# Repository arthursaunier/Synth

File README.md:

---
permalink: /index.html
layout: home
---

# This repo is being moved to an organization, there will be no new updates on this repo. For more informations, and with designs up to date, go to [BleepSound](https://github.com/orgs/BleepSound/repositories)

# Use all the designs here at your own risk, they have issues.

# Synth

## Not all projects are finished or even perfect, use at your own risks.

### VCOs:

- :exclamation: [CD40106-VCO](vco/cd40106)
    - CD40106 saw core oscillator based on Moritz Klein version (https://www.ericasynths.lv/shop/diy-kits-1/edu-diy-vco/)
        - 4 waveforms
            - Saw
            - Square with PWM control
            - Triangle
            - Sine
        - 5 octave switch
        - 1v/oct CV, FM CV and PWM CV.

### Effects:

- :warning: [StupidBox](stupidbox)
    - (messy directory but everything is there)
    - Size of panels and position is all wrong
    - Distortion module based on StupidBox stompbox design.
    - Vactrol CV to control distortion

### Filters:

- MS20-VCF
    - MS-20 clones built around the LM13700 chip
    - :warning: [Simple MS20 VCF](ms20_vcf/simple):
        - 1 LM13700 filter with a Low pass or High pass switch with CV for cutoff
        - Based on barton's version (https://www.bartonmusicalcircuits.com/synthstuff.html#analog))
    - :heavy_check_mark: [Double MS20-VCF](ms20_vcf/double)
        - 2 filters in one, each with Low pass or High pass with a possibility to bridge them and get a band pass filter with CV for cutoff
        - Based on barton's version (https://www.bartonmusicalcircuits.com/synthstuff.html#analog))

### Drums:

- :heavy_check_mark: [HiHat+Snare](hihat_snare/v1.1)
    - 2 white noise generators with VCAs to create Hihat or Snare sound.
    - Built on the same module, with 2 separate voices (completly independent)
    - No CV
- Drumbox
    - A 4 sounds drumbox built around the CD4011 chip. Bass kick, High and low bonga and claves sound.
    - :heavy_check_mark: V1.0:
        - Each voice has a seperate output.
    - :warning: [V1.2](drumbox):
        - Single main output for the module
        - Push buttons to trigger the voices. The buttons are from THONK (https://www.thonk.co.uk/shop/low-profile-led-buttons/)

### Mixers:

- :heavy_check_mark: [Basic AC mixer](mixers/basic-ac-mixer)
    - 4 channel active mixer with mute option with AC coupling (Audio only)
- :heavy_check_mark: [Basic DC mixer](mixers/basic-dc-mixer)
    - 4 channel active mixer with mute option with DC coupling (Audio+CV)
- Output mixer
    - :warning: [Mono input](mixers/output-mixer/mono_input):
        - 6 channels with 2 mono inputs each, gain and pan on each channel
        - stereo output in jack 3.5mm and jack 6.35mm
        - Headphone output with amp
    - :warning: [Stereo input](mixers/output-mixer/stereo_input):
        - 6 channels with stereo inputs, gain and pan on each channel
        - If only L or R plugged, act as a mono channel
        - stereo output in jack 3.5mm and jack 6.35mm
        - Headphone output with amp

### Multiple:

- :heavy_check_mark: [3x2 multiplexer](multiplexer/3x2)
    - 3x2 multiplexer (3 inputs to 2 output each)
    - cascade the first input to all outputs if no other input is plugged in

### Power delivery:

- :heavy_check_mark:  [PSU](power_supply/psu)
    - Basic +/- 12V power supply built around the L7812/7912 regulators.
-  :heavy_check_mark:  [Distribution board](power_supply/distributionboard)
    - Basic PSU distribution board, with 10 IDC headers.

### Sequencers:

- :exclamation: [Drum trigger sequencer](trigger_sequencer)
    - Based off the Big Button from LMNC, with an arduino Nano.
    - No code developped yet
    - Not finished and probably never will :)

| Symbol | Description |
| ----------- | ----------- |
| :heavy_check_mark: | Fully designed, debugged, tested, and verified. |
| :warning: | Fully designed but not tested. There is a high chance this won't work first try. |
| :exclamation: | Unfinished, messy design. Do not use, for reference or otherwise. |

*Cheers to @Sonosus for the labeling idea*

This work is licensed under a [Creative Commons Attribution-ShareAlike 4.0 International License.](http://creativecommons.org/licenses/by-sa/4.0/)

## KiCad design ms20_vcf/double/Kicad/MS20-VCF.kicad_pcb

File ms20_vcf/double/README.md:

---
permalink: /ms20_vcf/double/index.html
layout: single
---

# Double MS20 VCF

2 filters in one with a possibility to bridge them and get a band pass filter.

When using the band pass mode, signal IN on filter 1 and out on filter 2.

For each filter :

- Ms20-VCF clone based on BartonSynth version.

- cutoff + resonance, with a switch to chose low pass or high pass mode.

- CV control on the filter cutoff.

- Self oscilation if resonance pushed to maximum, can be adjusted with 2 trimmers  on each filter.

    - 1 trimmer for the sine wave amplitude (resVol)
    - 1 trimmer for the level at which the knob for resonance starts the self oscillation (resLvl)

Uses an DIP LM13700 not produced anymore, Will do an SMD version soon.

Regular build, I use ceramic capacitors but you can use film/polyester.

[See bom](bom/ibom.html)

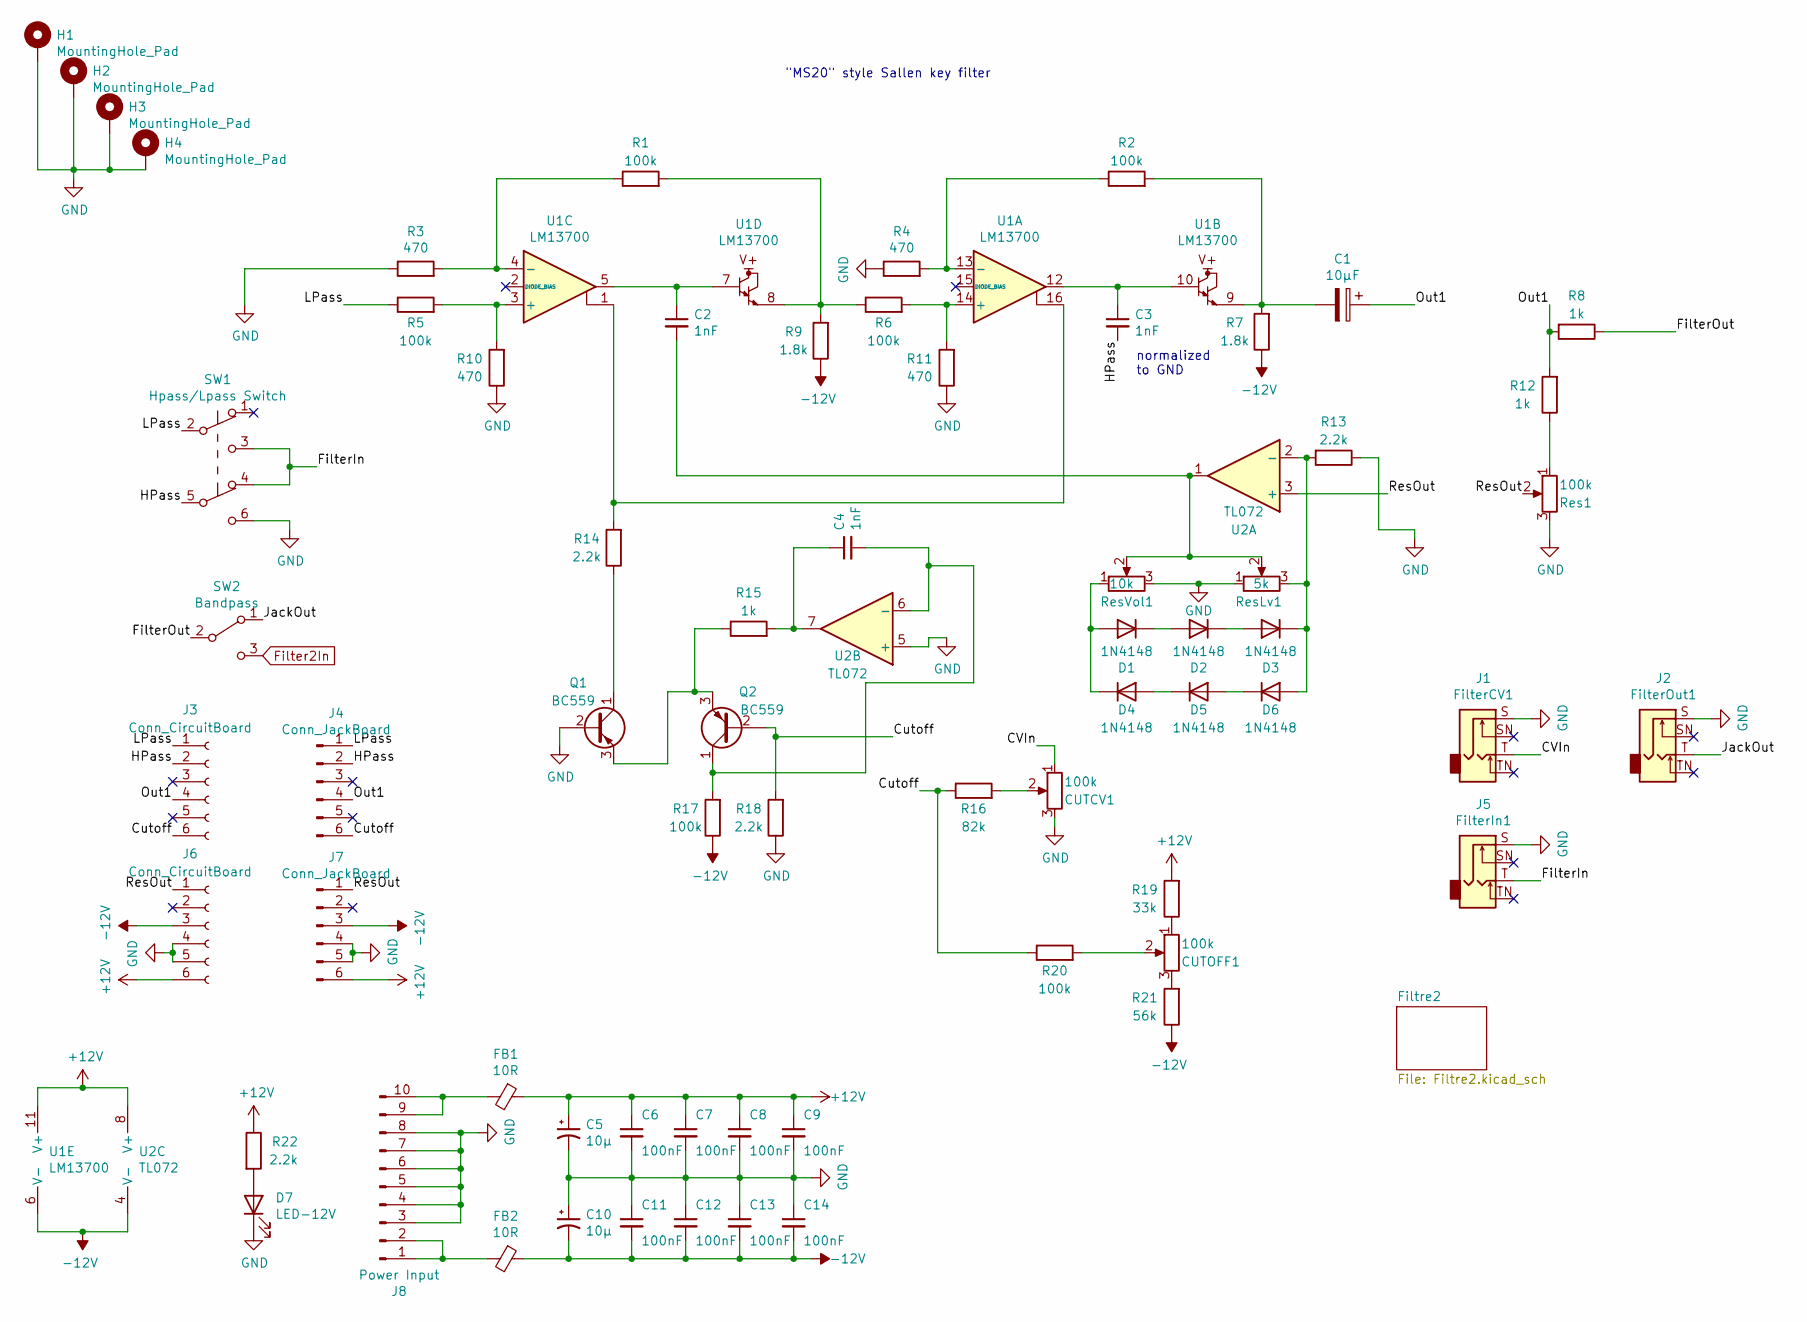
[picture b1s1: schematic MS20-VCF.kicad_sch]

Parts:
C1: 10µF; CP_Radial_D5.0mm_P2.00mm
C2, C3, C4: 1nF; C_Disc_D7.0mm_W2.5mm_P5.00mm
C5, C10: 10µ; CP_Radial_D5.0mm_P2.00mm
C6, C7, C8, C9, C11, C12, C13, C14: 100nF; C_Disc_D7.0mm_W2.5mm_P5.00mm
CUTCV1: 100k; Pot-bourns-alpha
CUTOFF1: 100k; Pot-bourns-alpha
D1, D2, D3, D4, D5, D6: 1N4148; D_DO-35_SOD27_P7.62mm_Horizontal
D7: LED-12V; LED_D4.0mm
FB1, FB2: 10R; L_Axial_L7.0mm_D3.3mm_P10.16mm_Horizontal_Fastron_MICC
H1, H2, H3, H4: MountingHole_Pad; Doepfer Mounting hole
J1: FilterCV1; Thonkiconn
J2: FilterOut1; Thonkiconn
J3, J6: Conn_CircuitBoard; PinSocket_1x06_P2.54mm_Vertical
J4, J7: Conn_JackBoard; PinHeader_1x06_P2.54mm_Vertical
J5: FilterIn1; Thonkiconn
J8: Power Input; IDC-Header_2x05_P2.54mm_Vertical
Q1, Q2: BC559; TO-92_Inline_Wide
R1, R2, R5, R6, R17, R20: 100k; R_Axial_DIN0207_L6.3mm_D2.5mm_P10.16mm_Horizontal
R3, R4, R10, R11: 470; R_Axial_DIN0207_L6.3mm_D2.5mm_P10.16mm_Horizontal
R7, R9: 1.8k; R_Axial_DIN0207_L6.3mm_D2.5mm_P10.16mm_Horizontal
R8, R12, R15: 1k; R_Axial_DIN0207_L6.3mm_D2.5mm_P10.16mm_Horizontal
R13, R14, R18, R22: 2.2k; R_Axial_DIN0207_L6.3mm_D2.5mm_P10.16mm_Horizontal
R16: 82k; R_Axial_DIN0207_L6.3mm_D2.5mm_P10.16mm_Horizontal
R19: 33k; R_Axial_DIN0207_L6.3mm_D2.5mm_P10.16mm_Horizontal
R21: 56k; R_Axial_DIN0207_L6.3mm_D2.5mm_P10.16mm_Horizontal
Res1: 100k; Pot-bourns-alpha
ResLv1: 5k; Potentiometer_Bourns_3386X_Horizontal
ResVol1: 10k; Potentiometer_Bourns_3386X_Horizontal
SW1: Hpass/Lpass Switch; SW_DPDT_Toggle
SW2: Bandpass; SW_Toggle_Blue_wSlots
U1: LM13700; SOIC-16_3.9x9.9mm_P1.27mm
U2: TL072; DIP-8_W7.62mm_Socket

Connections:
+12V: C5.1, C6.1, C7.1, C8.1, C9.1, FB1.1, J6.6, J7.6, R19.2, R22.1, U1.11 (V+), U2.8 (V+); also elsewhere on the board
-12V: C10.2, C11.2, C12.2, C13.2, C14.2, FB2.1, J6.3, J7.3, R7.1, R9.1, R17.1, R21.1, U1.6 (V-), U2.4 (V-); also elsewhere on the board
/CVIn: CUTCV1.1, J1.T
/Cutoff: J3.6, J4.6, Q2.2 (B), R16.1, R18.2, R20.1
/FilterIn: J5.T, SW1.3 (C), SW1.4 (A)
/FilterOut: R8.1, SW2.2 (B)
/HPass: C3.2, J3.2, J4.2, SW1.5 (B)
/JackOut: J2.T, SW2.1 (A)
/LPass: J3.1, J4.1, R5.1, SW1.2 (B)
/Out1: C1.1, J3.4, J4.4, R8.2, R12.2
/ResOut: J6.1, J7.1, Res1.2, U2.3 (+)
Filter2In: SW2.3 (C); also elsewhere on the board
GND: C5.2, C6.2, C7.2, C8.2, C9.2, C10.1, C11.1, C12.1, C13.1, C14.1, CUTCV1.3, D7.1 (K), H1.1, H2.1, H3.1, H4.1, J1.S, J2.S, J5.S, J6.4, J6.5, J7.4, J7.5, J8.3, J8.4, J8.5, J8.6, J8.7, J8.8, Q1.2 (B), R3.1, R4.1, R10.1, R11.1, R13.1, R18.1, Res1.3, ResLv1.1, ResVol1.3, SW1.6 (C), U2.5 (+); also elsewhere on the board
unnamed: C1.2, R2.2, R7.2, U1.9
unnamed: C2.1, U1.5, U1.7
unnamed: C2.2, ResLv1.2, ResVol1.2, U2.1
unnamed: C3.1, U1.10, U1.12
unnamed: C4.1, R15.2, U2.7
unnamed: C4.2, Q2.1 (C), R17.2, U2.6 (-)
unnamed: CUTCV1.2, R16.2
unnamed: CUTOFF1.1, R19.1
unnamed: D1.1 (K), D2.2 (A)
unnamed: D1.2 (A), D4.1 (K), ResVol1.1
unnamed: D2.1 (K), D3.2 (A)
unnamed: D3.1 (K), D6.2 (A), R13.2, ResLv1.3, U2.2 (-)
unnamed: D4.2 (A), D5.1 (K)
unnamed: D5.2 (A), D6.1 (K)
unnamed: D7.2 (A), R22.2
unnamed: FB1.2, J8.9, J8.10
unnamed: FB2.2, J8.1, J8.2
unnamed: Q1.1 (C), R14.1
unnamed: Q1.3 (E), Q2.3 (E), R15.1
unnamed: R1.1, R3.2, U1.4 (-)
unnamed: R1.2, R6.1, R9.2, U1.8
unnamed: R2.1, R4.2, U1.13 (-)
unnamed: R5.2, R10.2, U1.3 (+)
unnamed: R6.2, R11.2, U1.14 (+)
unnamed: R12.1, Res1.1
unnamed: R14.2, U1.1, U1.16
unnamed: CUTOFF1.2, R20.2
unnamed: CUTOFF1.3, R21.2

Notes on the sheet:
normalized to GND
"MS20" style Sallen key filter

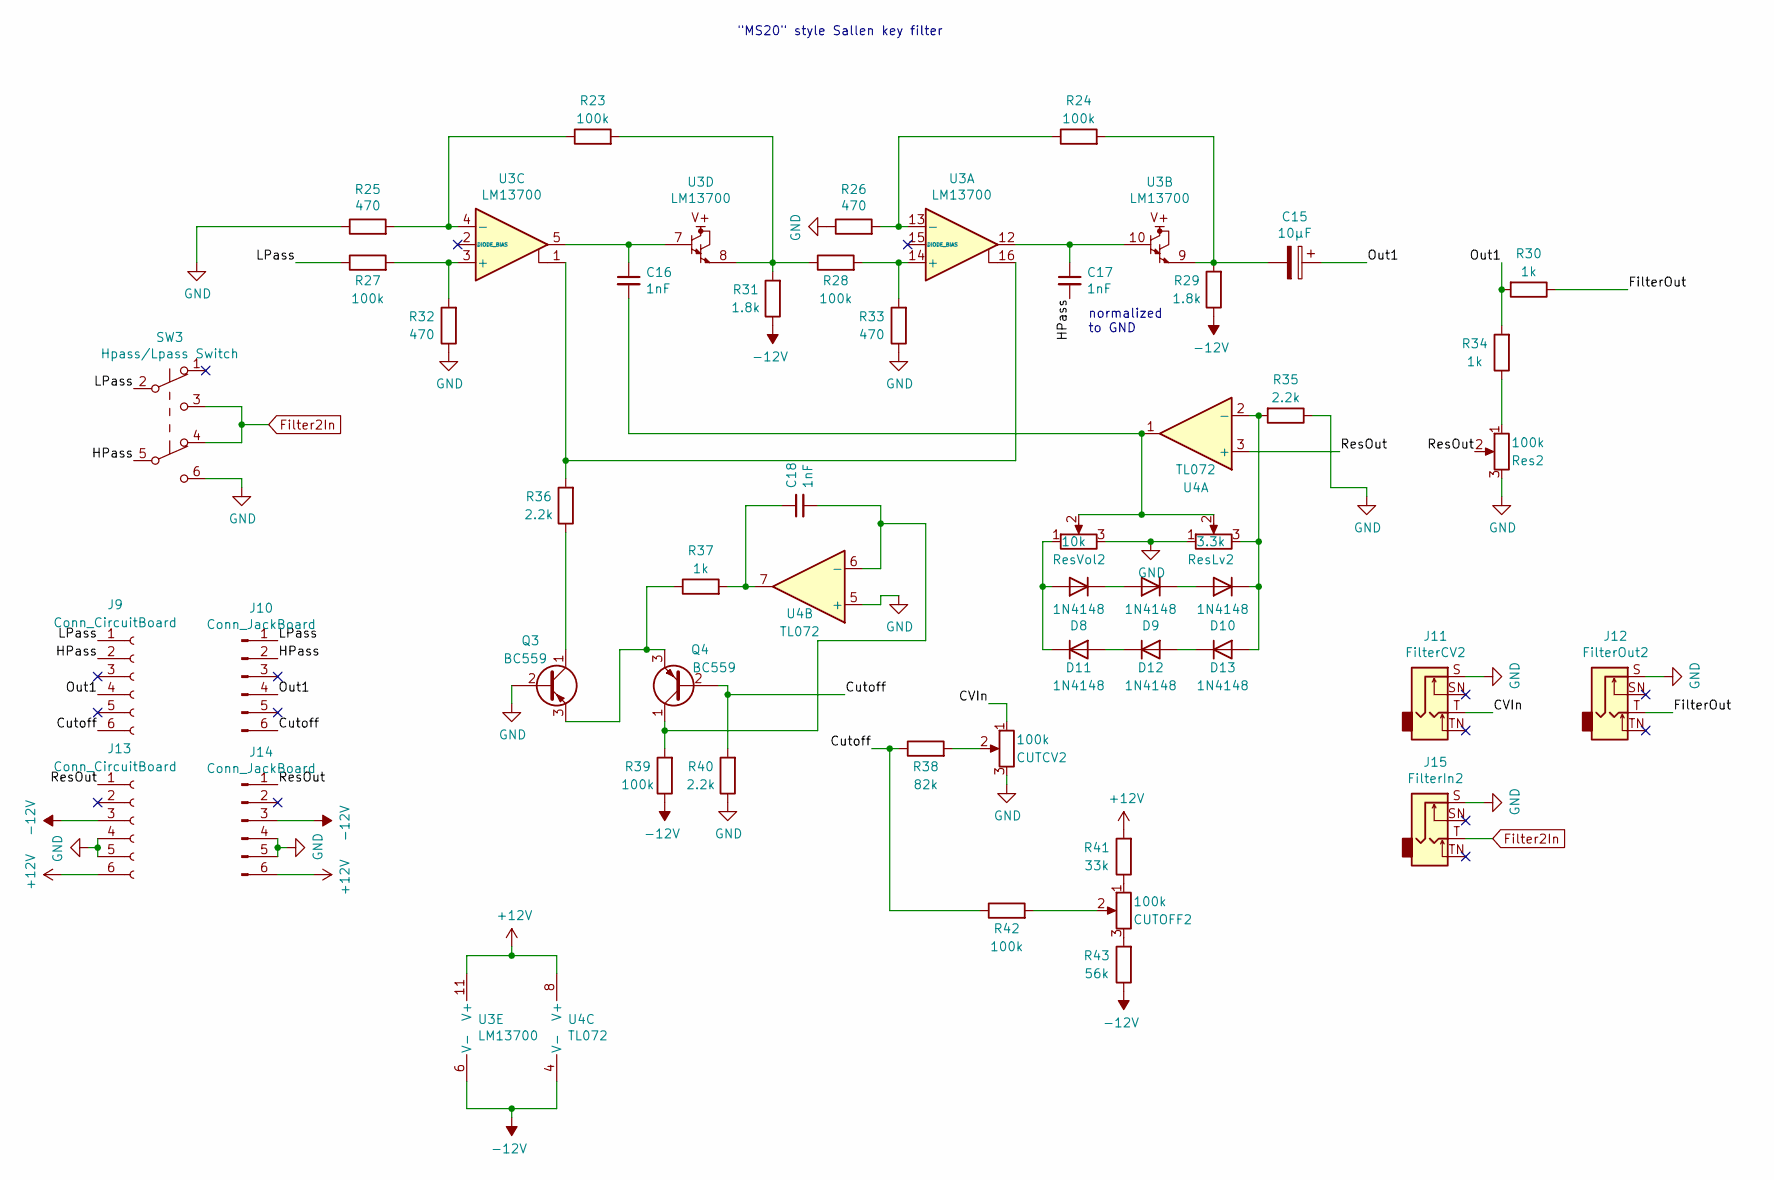
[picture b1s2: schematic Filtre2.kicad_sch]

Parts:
C15: 10µF; CP_Radial_D5.0mm_P2.00mm
C16, C17, C18: 1nF; C_Disc_D7.0mm_W2.5mm_P5.00mm
CUTCV2: 100k; Pot-bourns-alpha
CUTOFF2: 100k; Pot-bourns-alpha
D8, D9, D10, D11, D12, D13: 1N4148; D_DO-35_SOD27_P7.62mm_Horizontal
J9, J13: Conn_CircuitBoard; PinSocket_1x06_P2.54mm_Vertical
J10, J14: Conn_JackBoard; PinHeader_1x06_P2.54mm_Vertical
J11: FilterCV2; Thonkiconn
J12: FilterOut2; Thonkiconn
J15: FilterIn2; Thonkiconn
Q3, Q4: BC559; TO-92_Inline_Wide
R23, R24, R27, R28, R39, R42: 100k; R_Axial_DIN0207_L6.3mm_D2.5mm_P10.16mm_Horizontal
R25, R26, R32, R33: 470; R_Axial_DIN0207_L6.3mm_D2.5mm_P10.16mm_Horizontal
R29, R31: 1.8k; R_Axial_DIN0207_L6.3mm_D2.5mm_P10.16mm_Horizontal
R30, R34, R37: 1k; R_Axial_DIN0207_L6.3mm_D2.5mm_P10.16mm_Horizontal
R35, R36, R40: 2.2k; R_Axial_DIN0207_L6.3mm_D2.5mm_P10.16mm_Horizontal
R38: 82k; R_Axial_DIN0207_L6.3mm_D2.5mm_P10.16mm_Horizontal
R41: 33k; R_Axial_DIN0207_L6.3mm_D2.5mm_P10.16mm_Horizontal
R43: 56k; R_Axial_DIN0207_L6.3mm_D2.5mm_P10.16mm_Horizontal
Res2: 100k; Pot-bourns-alpha
ResLv2: 3.3k; Potentiometer_Bourns_3386X_Horizontal
ResVol2: 10k; Potentiometer_Bourns_3386X_Horizontal
SW3: Hpass/Lpass Switch; SW_DPDT_Toggle
U3: LM13700; SOIC-16_3.9x9.9mm_P1.27mm
U4: TL072; DIP-8_W7.62mm_Socket

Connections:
+12V: J13.6, J14.6, R41.2, U3.11 (V+), U4.8 (V+); also elsewhere on the board
-12V: J13.3, J14.3, R29.1, R31.1, R39.1, R43.1, U3.6 (V-), U4.4 (V-); also elsewhere on the board
/Filtre2/CVIn: CUTCV2.1, J11.T
/Filtre2/Cutoff: J9.6, J10.6, Q4.2 (B), R38.1, R40.2, R42.1
/Filtre2/FilterOut: J12.T, R30.1
/Filtre2/HPass: C17.2, J9.2, J10.2, SW3.5 (B)
/Filtre2/LPass: J9.1, J10.1, R27.1, SW3.2 (B)
/Filtre2/Out1: C15.1, J9.4, J10.4, R30.2, R34.2
/Filtre2/ResOut: J13.1, J14.1, Res2.2, U4.3 (+)
Filter2In: J15.T, SW3.3 (C), SW3.4 (A); also elsewhere on the board
GND: CUTCV2.3, J11.S, J12.S, J13.4, J13.5, J14.4, J14.5, J15.S, Q3.2 (B), R25.1, R26.1, R32.1, R33.1, R35.1, R40.1, Res2.3, ResLv2.1, ResVol2.3, SW3.6 (C), U4.5 (+); also elsewhere on the board
unnamed: C15.2, R24.2, R29.2, U3.9
unnamed: C16.1, U3.5, U3.7
unnamed: C16.2, ResLv2.2, ResVol2.2, U4.1
unnamed: C17.1, U3.10, U3.12
unnamed: C18.1, R37.2, U4.7
unnamed: C18.2, Q4.1 (C), R39.2, U4.6 (-)
unnamed: CUTCV2.2, R38.2
unnamed: CUTOFF2.1, R41.1
unnamed: CUTOFF2.2, R42.2
unnamed: CUTOFF2.3, R43.2
unnamed: D8.1 (K), D9.2 (A)
unnamed: D10.1 (K), D13.2 (A), R35.2, ResLv2.3, U4.2 (-)
unnamed: D9.1 (K), D10.2 (A)
unnamed: D8.2 (A), D11.1 (K), ResVol2.1
unnamed: D11.2 (A), D12.1 (K)
unnamed: D12.2 (A), D13.1 (K)
unnamed: Q3.1 (C), R36.1
unnamed: Q3.3 (E), Q4.3 (E), R37.1
unnamed: R23.1, R25.2, U3.4 (-)
unnamed: R23.2, R28.1, R31.2, U3.8
unnamed: R24.1, R26.2, U3.13 (-)
unnamed: R27.2, R32.2, U3.3 (+)
unnamed: R28.2, R33.2, U3.14 (+)
unnamed: R34.1, Res2.1
unnamed: R36.2, U3.1, U3.16

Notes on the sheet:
normalized to GND
"MS20" style Sallen key filter

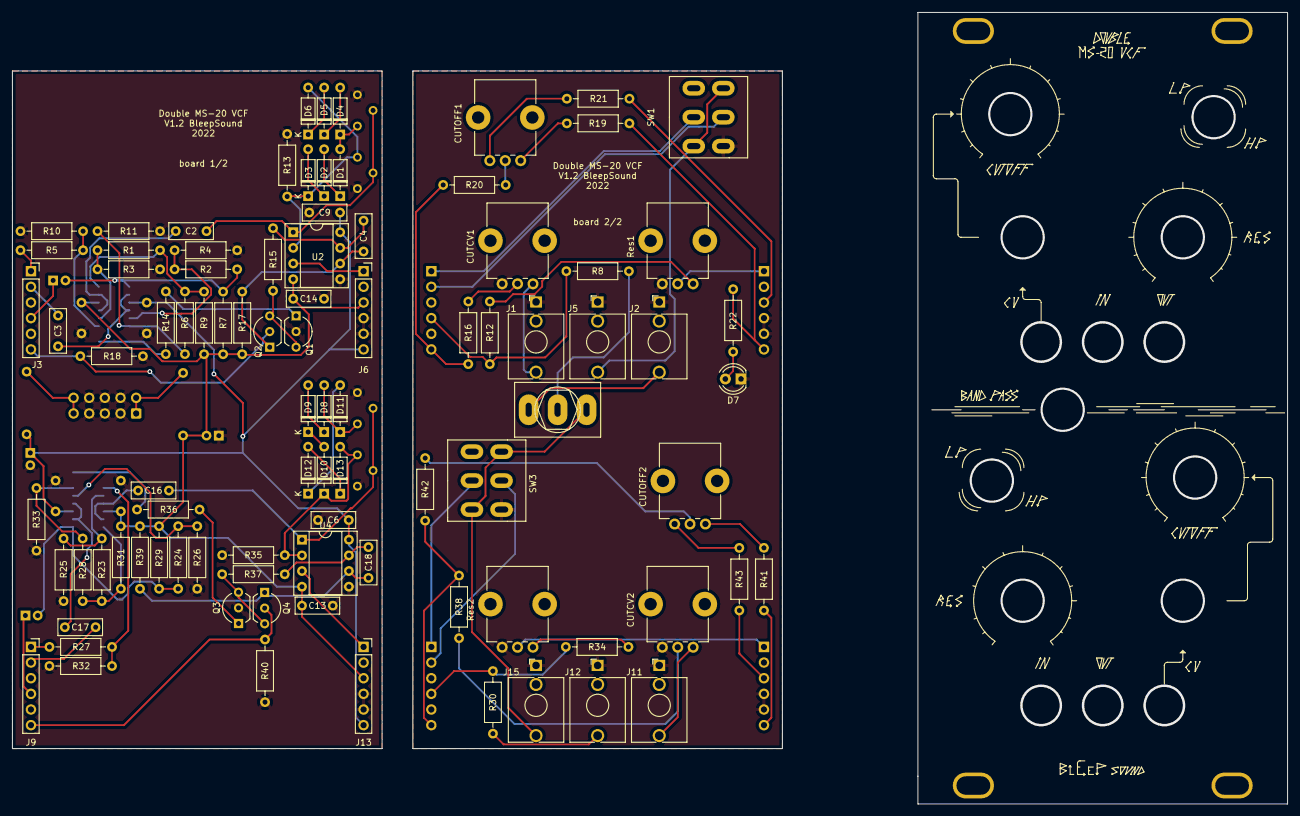
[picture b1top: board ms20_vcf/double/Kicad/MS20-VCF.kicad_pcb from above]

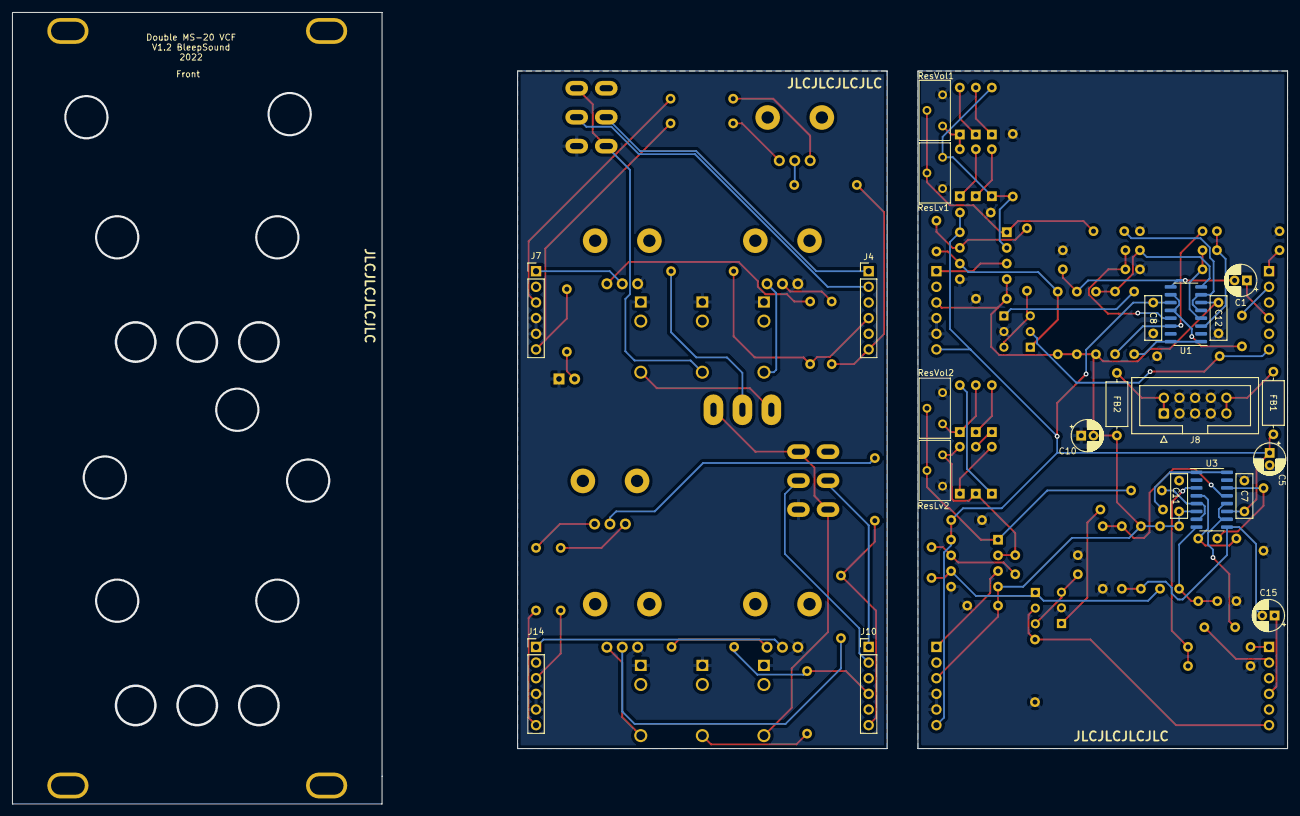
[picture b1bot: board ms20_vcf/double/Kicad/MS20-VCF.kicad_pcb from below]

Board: 2 copper layers, 207.0 x 128.5 mm, 116 parts (21 on the bottom side), 73 nets.

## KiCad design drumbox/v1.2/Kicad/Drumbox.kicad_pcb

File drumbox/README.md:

# Drumbox

## V1.0

A 4 sounds drumbox built around the CD4011 chip. Bass kick, High and low bonga and claves sound.

Each voice has a seperate output.

No CV

## V1.1

Single main output for the module

Push buttons to trigger the voices. The buttons are from THONK (https://www.thonk.co.uk/shop/low-profile-led-buttons/)

## V1.2

This version adds a gain change of the output buffers on each voice.

[See bom](v1.2/bom/ibom.html)

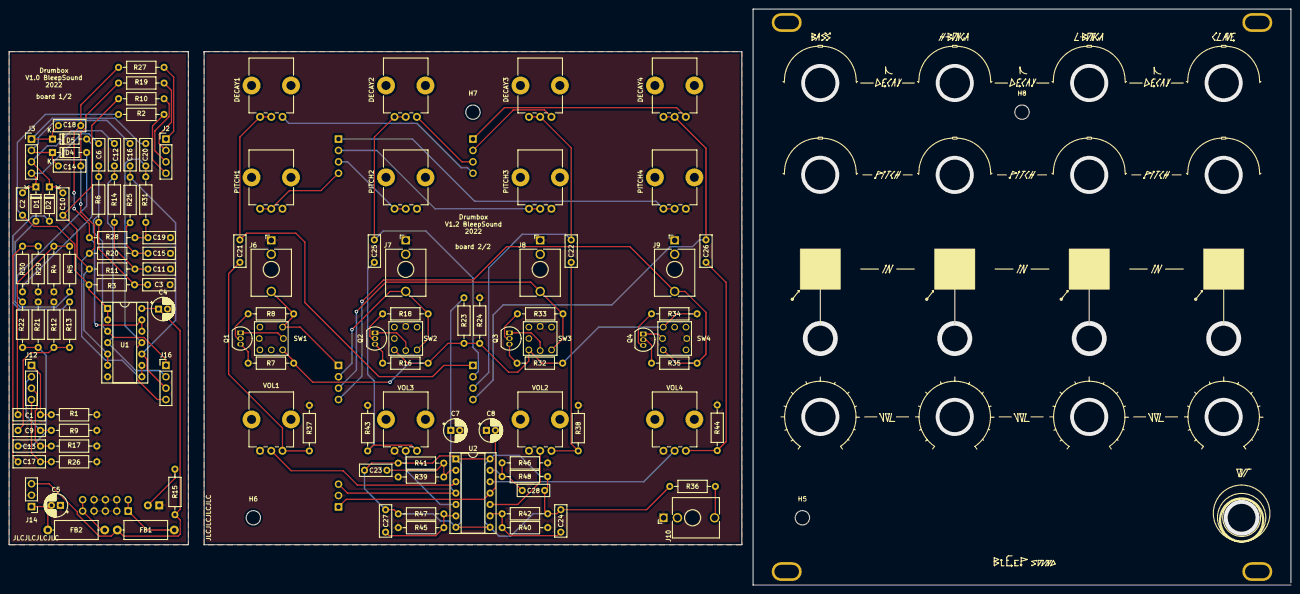
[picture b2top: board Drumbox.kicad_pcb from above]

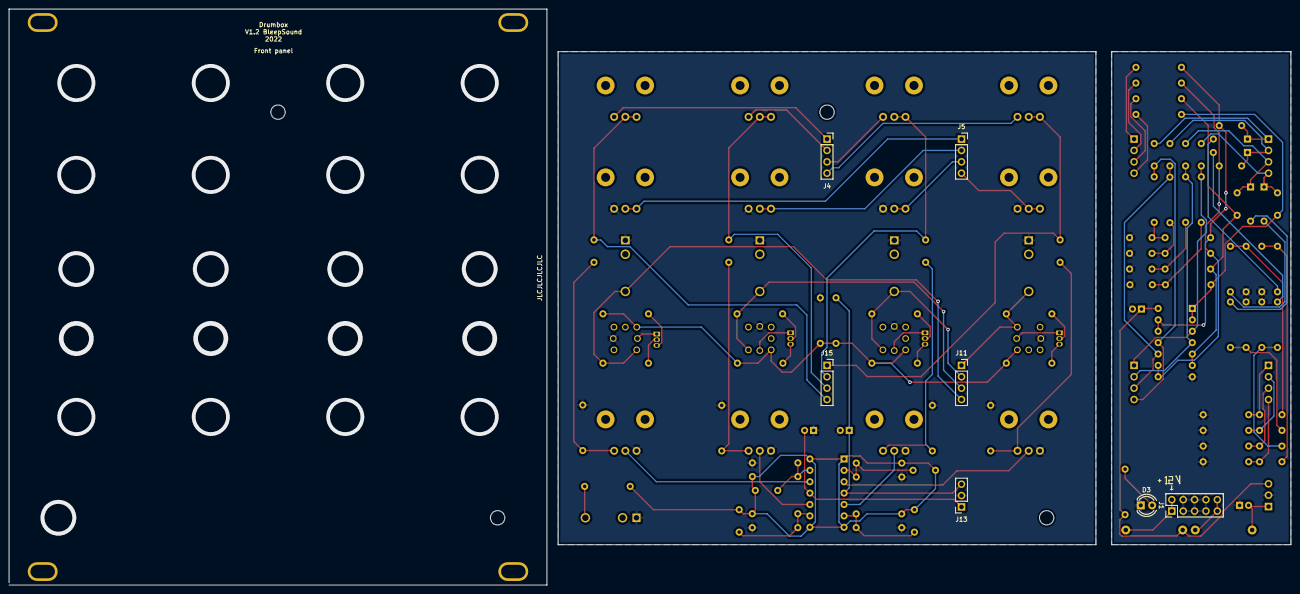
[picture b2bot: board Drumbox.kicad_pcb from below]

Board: 2 copper layers, 286.0 x 128.5 mm, 129 parts (7 on the bottom side), 65 nets.

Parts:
C1, C3: 150nF; C_Disc_D7.0mm_W2.5mm_P5.00mm
C2, C6: 47nF; C_Disc_D7.0mm_W2.5mm_P5.00mm
C4, C5: 10µ; CP_Radial_D5.0mm_P2.00mm
C7, C8: 100n; CP_Radial_D5.0mm_P2.00mm
C9, C11: 33nF; C_Disc_D7.0mm_W2.5mm_P5.00mm
C10, C12: 10nF; C_Disc_D7.0mm_W2.5mm_P5.00mm
C13, C15: 39nF; C_Disc_D7.0mm_W2.5mm_P5.00mm
C14, C16: 12nF; C_Disc_D7.0mm_W2.5mm_P5.00mm
C17: 4.7nF; C_Disc_D7.0mm_W2.5mm_P5.00mm
C18, C20: 1.5nF; C_Disc_D7.0mm_W2.5mm_P5.00mm
C19: 56nF; C_Disc_D7.0mm_W2.5mm_P5.00mm
C21, C22, C25, C26: .1µF; C_Disc_D7.0mm_W2.5mm_P5.00mm
C23, C24, C27, C28: 22pF; C_Disc_D7.0mm_W2.5mm_P5.00mm
D1, D2, D4, D5: 1N4148; D_DO-35_SOD27_P7.62mm_Horizontal
D3: LED-12V; LED_D4.0mm
DECAY1, DECAY2, DECAY3, DECAY4: 470k; Potentiometer_Bourns_PTV09A-1_Single_Vertical
FB1, FB2: 10R; L_Axial_L9.5mm_D4.0mm_P12.70mm_Horizontal_Fastron_SMCC
H1, H2, H3, H4: MountingHole; Doepfer Mounting hole
H5, H6, H7, H8: SpacerHoles; MountingHole_3.2mm_M3
J1: Power Input; PinHeader_2x05_P2.54mm_Vertical
J2, J3, J12, J16: Conn_01x04_Male; PinHeader_1x04_P2.54mm_Vertical
J4, J5, J11, J15: Conn_01x04_Female; PinSocket_1x04_P2.54mm_Vertical
J6: Bass IN; Jack_3.5mm_QingPu_WQP-PJ398SM_Vertical_CircularHoles
J7: HBonga IN; Jack_3.5mm_QingPu_WQP-PJ398SM_Vertical_CircularHoles
J8: LBonga IN; Jack_3.5mm_QingPu_WQP-PJ398SM_Vertical_CircularHoles
J9: Clave IN; Jack_3.5mm_QingPu_WQP-PJ398SM_Vertical_CircularHoles
J10: Main OUT; Jack_3.5mm_QingPu_WQP-PJ398SM_Vertical_CircularHoles
J13: Conn_01x03_Female; PinSocket_1x03_P2.54mm_Vertical
J14: Conn_01x03_Male; PinHeader_1x03_P2.54mm_Vertical
PITCH1, PITCH2, PITCH3, PITCH4: 10k; Potentiometer_Bourns_PTV09A-1_Single_Vertical
Q1, Q2, Q3, Q4: 2N3904; TO-92_Inline
R1, R9, R17, R26: 12k; R_Axial_DIN0207_L6.3mm_D2.5mm_P10.16mm_Horizontal
R2, R10, R19, R27: 150k; R_Axial_DIN0207_L6.3mm_D2.5mm_P10.16mm_Horizontal
R3, R6, R11, R14, R20, R25, R28, R31: 68k; R_Axial_DIN0207_L6.3mm_D2.5mm_P10.16mm_Horizontal
R4, R12, R21, R23, R29: 47k; R_Axial_DIN0207_L6.3mm_D2.5mm_P10.16mm_Horizontal
R5, R13, R22, R30: 27k; R_Axial_DIN0207_L6.3mm_D2.5mm_P10.16mm_Horizontal
R7, R16, R32, R34, R36: 1k; R_Axial_DIN0207_L6.3mm_D2.5mm_P10.16mm_Horizontal
R8, R18, R33, R35, R41, R42, R47, R48: 100k; R_Axial_DIN0207_L6.3mm_D2.5mm_P10.16mm_Horizontal
R15: 2.2k; R_Axial_DIN0207_L6.3mm_D2.5mm_P10.16mm_Horizontal
R24: 33k; R_Axial_DIN0207_L6.3mm_D2.5mm_P10.16mm_Horizontal
R37, R38, R43, R44: 1M; R_Axial_DIN0207_L6.3mm_D2.5mm_P10.16mm_Horizontal
R39: 10k; R_Axial_DIN0207_L6.3mm_D2.5mm_P10.16mm_Horizontal
R40, R45, R46: 20k; R_Axial_DIN0207_L6.3mm_D2.5mm_P10.16mm_Horizontal
SW1, SW2, SW3, SW4: SW_MEC_LOW_PROF_LED; PB01-109TL
U1: 4011; DIP-14_W7.62mm_Socket
U2: TL074; DIP-14_W7.62mm_Socket
VOL1, VOL2, VOL3, VOL4: 10k; Potentiometer_Bourns_PTV09A-1_Single_Vertical

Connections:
+5V: R7.1, R16.1, R23.2, R24.1, R32.1, R34.1, SW1.1, SW2.1, SW3.1, SW4.1
+12V: C4.1, C7.1, FB1.1, J13.3, J14.3, R15.1, R23.1, U1.14 (VDD), U2.4 (V+)
-12V: C5.2, C8.2, FB2.1, J13.1, J14.1, U2.11 (V-)
DEIn1: DECAY1.1, J2.4, J4.4, R2.1
DEIn2: DECAY2.1, J2.3, J4.3, R10.1
DEIn3: DECAY3.1, J2.2, J4.2, R19.1
DEIn4: DECAY4.1, J2.1, J4.1, R27.1
GND: C3.2, C4.2, C5.1, C7.2, C8.1, C11.2, C15.2, C19.2, D3.1 (K), J1.3, J1.4, J1.5, J1.6, J1.7, J1.8, J6.S, J7.S, J8.S, J9.S, J10.S, J13.2, J14.2, PITCH1.1, PITCH2.1, PITCH3.1, PITCH4.1, R1.2, R4.1, R9.2, R12.1, R17.2, R21.1, R24.2, R26.2, R29.1, R37.2, R38.2, R39.2, R40.2, R43.2, R44.2, R45.2, R46.2, SW1.L2, SW2.L2, SW3.L2, SW4.L2, U1.7 (VSS), VOL1.3, VOL2.3, VOL3.3, VOL4.3
In1: C1.1, J6.T, J11.1, J12.1, R1.1, R8.1, SW1.3
In2: C9.1, J7.T, J11.2, J12.2, R9.1, R18.1, SW2.3
In3: C13.1, J8.T, J11.3, J12.3, R17.1, R33.1, SW3.3
In4: C17.1, J9.T, J11.4, J12.4, R26.1, R35.1, SW4.3
unnamed: C1.2, R4.2, R5.1
unnamed: C2.1, R2.2, R3.2, U1.1, U1.2
unnamed: C3.1, R3.1, R6.2
unnamed: C9.2, R12.2, R13.1
unnamed: C10.1, R10.2, R11.2, U1.5, U1.6
unnamed: C11.1, R11.1, R14.2
unnamed: C13.2, R21.2, R22.1
unnamed: C14.1, R19.2, R20.2, U1.8, U1.9
unnamed: C15.1, R20.1, R25.2
unnamed: C17.2, R29.2, R30.1
unnamed: C18.1, R27.2, R28.2, U1.12, U1.13
unnamed: C19.1, R28.1, R31.2
unnamed: C21.2, R37.1, VOL1.1
unnamed: C22.2, R38.1, VOL2.1
unnamed: C23.1, R39.1, R41.2, U2.2 (-)
unnamed: C24.1, R40.1, R42.2, U2.9 (-)
unnamed: C25.2, R43.1, VOL3.1
unnamed: C26.2, R44.1, VOL4.1
unnamed: C27.1, R45.1, R47.2, U2.6 (-)
unnamed: C28.1, R46.1, R48.2, U2.13 (-)
unnamed: D1.2 (A), R5.2
unnamed: D2.2 (A), R13.2
unnamed: D3.2 (A), R15.2
unnamed: D4.2 (A), R22.2
unnamed: D5.2 (A), R30.2
unnamed: FB1.2, J1.1, J1.2
unnamed: FB2.2, J1.9, J1.10
unnamed: J10.T, R36.1
unnamed: Q1.1 (E), SW1.L1
unnamed: Q1.2 (B), R8.2
unnamed: Q1.3 (C), R7.2
unnamed: Q2.1 (E), SW2.L1
unnamed: Q2.2 (B), R18.2
unnamed: Q2.3 (C), R16.2
unnamed: Q3.1 (E), SW3.L1
unnamed: Q3.2 (B), R33.2
unnamed: Q3.3 (C), R32.2
unnamed: Q4.1 (E), SW4.L1
unnamed: Q4.2 (B), R35.2
unnamed: Q4.3 (C), R34.2
unnamed: U2.3 (+), VOL1.2
unnamed: U2.5 (+), VOL3.2
unnamed: U2.10 (+), VOL2.2
unnamed: U2.12 (+), VOL4.2
O1: C6.2, C21.1, DECAY1.2, DECAY1.3, J15.1, J16.1, R6.1, U1.3
O2: C12.2, C25.1, DECAY2.2, DECAY2.3, J15.2, J16.2, R14.1, U1.4
O3: C16.2, C22.1, DECAY3.2, DECAY3.3, J15.3, J16.3, R25.1, U1.10
O4: C20.2, C26.1, DECAY4.2, DECAY4.3, J15.4, J16.4, R31.1, U1.11
Out1: C23.2, C24.2, C27.2, C28.2, R36.2, R41.1, R42.1, R47.1, R48.1, U2.1, U2.7, U2.8, U2.14
PIOut1: C2.2, C6.1, D1.1 (K), J3.4, J5.4, PITCH1.2, PITCH1.3
PIOut2: C10.2, C12.1, D2.1 (K), J3.3, J5.3, PITCH2.2, PITCH2.3
PIOut3: C14.2, C16.1, D4.1 (K), J3.2, J5.2, PITCH3.2, PITCH3.3
PIOut4: C18.2, C20.1, D5.1 (K), J3.1, J5.1, PITCH4.2, PITCH4.3

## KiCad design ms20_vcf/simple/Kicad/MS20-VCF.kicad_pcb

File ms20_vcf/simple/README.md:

---
permalink: /ms20_vcf/simple/index.html
layout: single
---

# MS20 VCF

Ms20-VCF clone based on BartonSynth version.

cutoff + resonance, with a switch to chose low pass or high pass mode.

CV control on the filter cutoff.

Self oscilation if resonance pushed to maximum, can be adjusted with 2 trimmers :

- 1 trimmer for the sine wave amplitude (resVol)
- 1 trimmer for the level at which the knob for resonance starts the self oscillation (resLvl)

Uses an SMD LM13700 because the DIP ones are not produced anymore.

Regular build, I use ceramic capacitors but you can use film/polyester.

[See bom](bom/ibom.html)

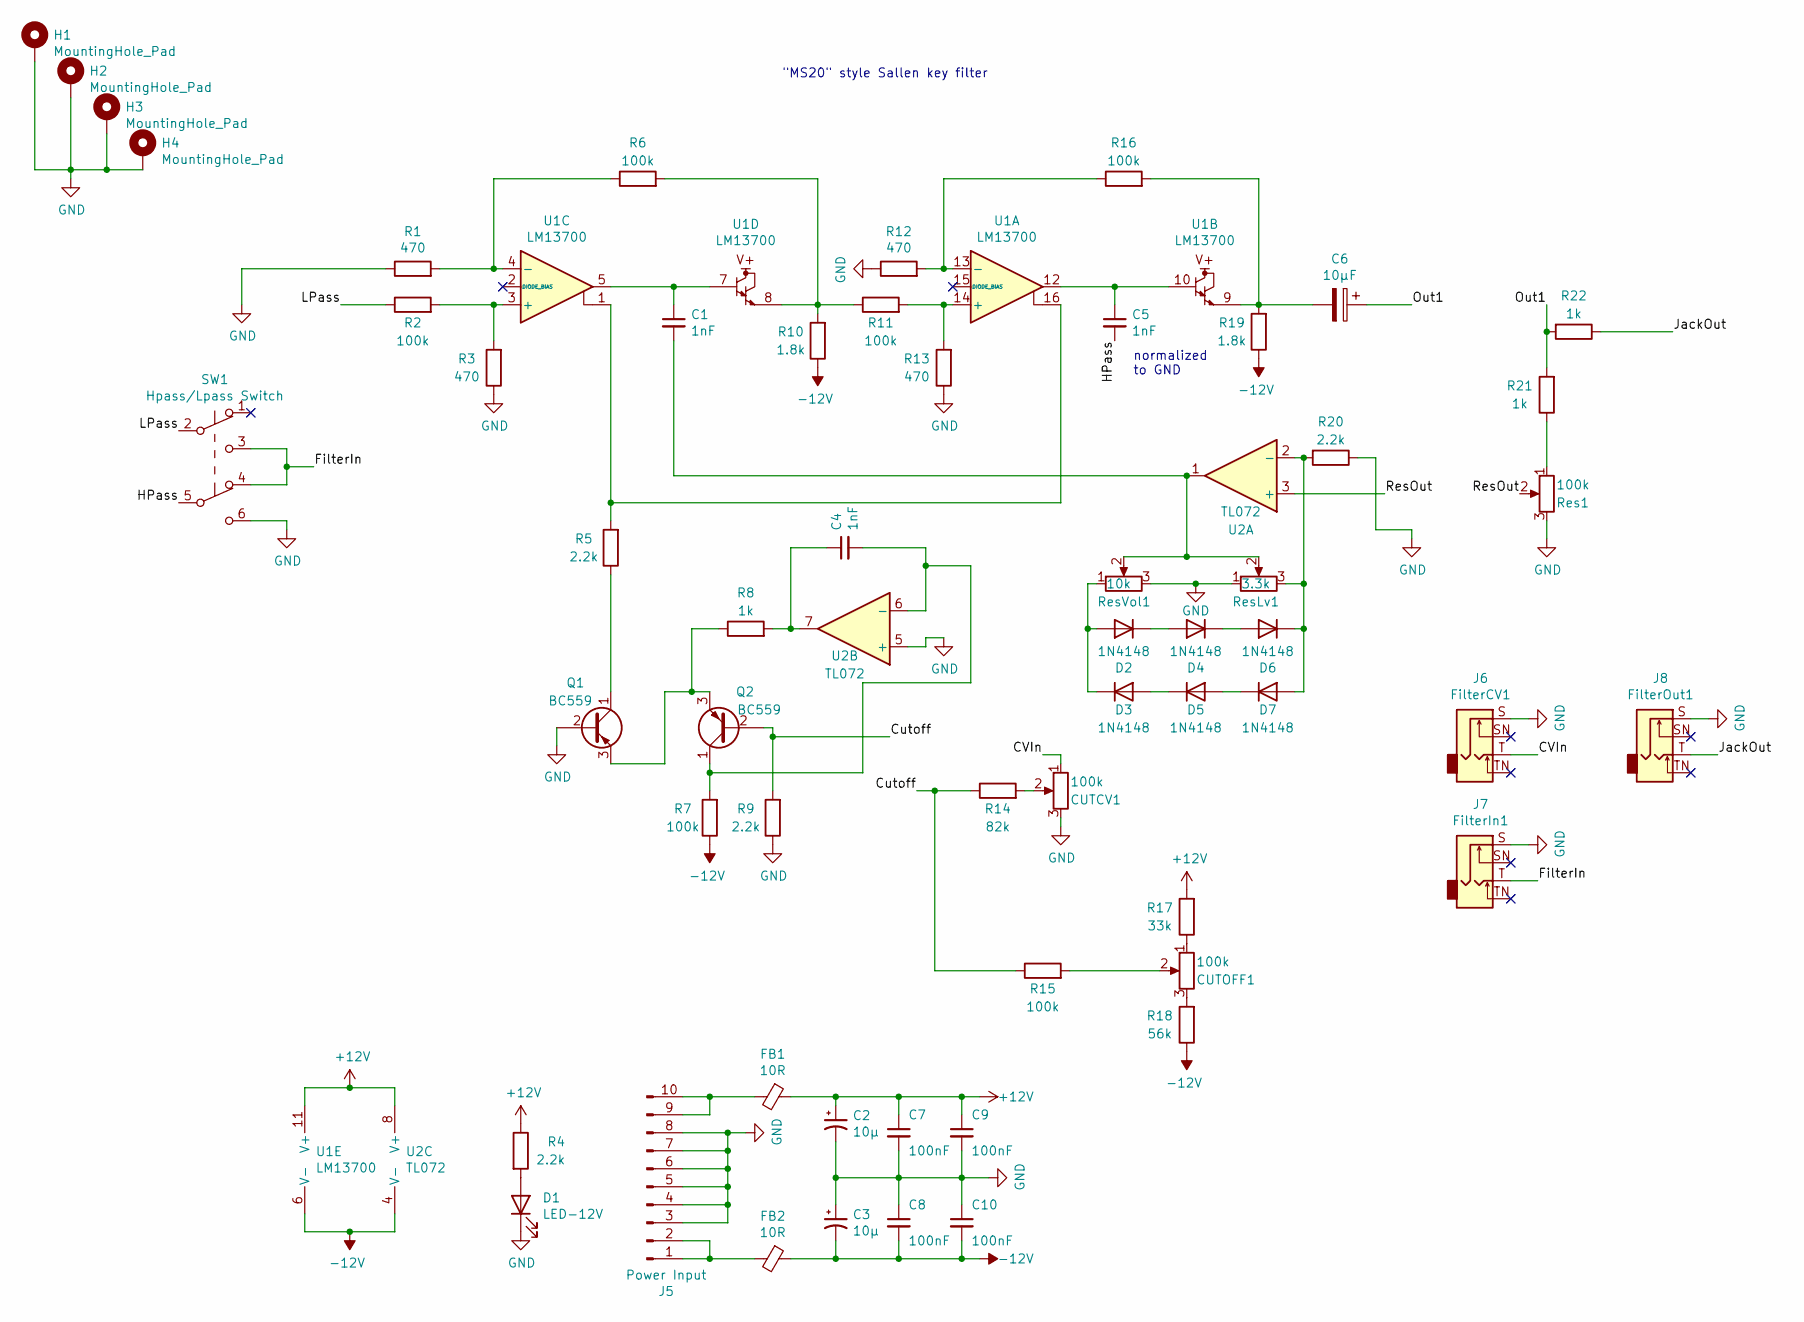
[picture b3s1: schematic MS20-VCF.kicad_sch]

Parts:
C1, C4, C5: 1nF; C_Disc_D7.0mm_W2.5mm_P5.00mm
C2, C3: 10µ; CP_Radial_D5.0mm_P2.00mm
C6: 10µF; CP_Radial_D5.0mm_P2.00mm
C7, C8, C9, C10: 100nF; C_Disc_D7.0mm_W2.5mm_P5.00mm
CUTCV1: 100k; Pot-bourns-alpha
CUTOFF1: 100k; Pot-bourns-alpha
D1: LED-12V; LED_D4.0mm
D2, D3, D4, D5, D6, D7: 1N4148; D_DO-35_SOD27_P7.62mm_Horizontal
FB1, FB2: 10R; L_Axial_L9.5mm_D4.0mm_P12.70mm_Horizontal_Fastron_SMCC
H1, H2, H3, H4: MountingHole_Pad; Doepfer Mounting hole
J5: Power Input; IDC-Header_2x05_P2.54mm_Vertical
J6: FilterCV1; Thonkiconn
J7: FilterIn1; Thonkiconn
J8: FilterOut1; Thonkiconn
Q1, Q2: BC559; TO-92_Inline_Wide
R1, R3, R12, R13: 470; R_Axial_DIN0207_L6.3mm_D2.5mm_P10.16mm_Horizontal
R2, R6, R7, R11, R15, R16: 100k; R_Axial_DIN0207_L6.3mm_D2.5mm_P10.16mm_Horizontal
R4, R5, R9, R20: 2.2k; R_Axial_DIN0207_L6.3mm_D2.5mm_P10.16mm_Horizontal
R8, R21, R22: 1k; R_Axial_DIN0207_L6.3mm_D2.5mm_P10.16mm_Horizontal
R10, R19: 1.8k; R_Axial_DIN0207_L6.3mm_D2.5mm_P10.16mm_Horizontal
R14: 82k; R_Axial_DIN0207_L6.3mm_D2.5mm_P10.16mm_Horizontal
R17: 33k; R_Axial_DIN0207_L6.3mm_D2.5mm_P10.16mm_Horizontal
R18: 56k; R_Axial_DIN0207_L6.3mm_D2.5mm_P10.16mm_Horizontal
Res1: 100k; Pot-bourns-alpha
ResLv1: 3.3k; Potentiometer_Bourns_3386C_Horizontal
ResVol1: 10k; Potentiometer_Bourns_3386C_Horizontal
SW1: Hpass/Lpass Switch; SW_DPDT_Toggle
U1: LM13700; SOIC-16_3.9x9.9mm_P1.27mm
U2: TL072; DIP-8_W7.62mm_Socket

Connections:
+12V: C2.1, C7.1, C9.1, FB1.1, R4.1, R17.2, U1.11 (V+), U2.8 (V+)
-12V: C3.2, C8.2, C10.2, FB2.1, R7.1, R10.1, R18.1, R19.1, U1.6 (V-), U2.4 (V-)
/CVIn: CUTCV1.1, J6.T
/Cutoff: Q2.2 (B), R9.2, R14.1, R15.1
/FilterIn: J7.T, SW1.3 (C), SW1.4 (A)
/HPass: C5.2, SW1.5 (B)
/JackOut: J8.T, R22.1
/LPass: R2.1, SW1.2 (B)
/Out1: C6.1, R21.2, R22.2
/ResOut: Res1.2, U2.3 (+)
GND: C2.2, C3.1, C7.2, C8.1, C9.2, C10.1, CUTCV1.3, D1.1 (K), H1.1, H2.1, H3.1, H4.1, J5.3, J5.4, J5.5, J5.6, J5.7, J5.8, J6.S, J7.S, J8.S, Q1.2 (B), R1.1, R3.1, R9.1, R12.1, R13.1, R20.1, Res1.3, ResLv1.1, ResVol1.3, SW1.6 (C), U2.5 (+)
unnamed: C1.1, U1.5, U1.7
unnamed: C1.2, ResLv1.2, ResVol1.2, U2.1
unnamed: C4.1, R8.2, U2.7
unnamed: C4.2, Q2.1 (C), R7.2, U2.6 (-)
unnamed: C5.1, U1.10, U1.12
unnamed: C6.2, R16.2, R19.2, U1.9
unnamed: CUTOFF1.1, R17.1
unnamed: D1.2 (A), R4.2
unnamed: D2.1 (K), D4.2 (A)
unnamed: D2.2 (A), D3.1 (K), ResVol1.1
unnamed: D3.2 (A), D5.1 (K)
unnamed: D4.1 (K), D6.2 (A)
unnamed: D5.2 (A), D7.1 (K)
unnamed: D6.1 (K), D7.2 (A), R20.2, ResLv1.3, U2.2 (-)
unnamed: FB1.2, J5.9, J5.10
unnamed: FB2.2, J5.1, J5.2
unnamed: Q1.1 (C), R5.1
unnamed: Q1.3 (E), Q2.3 (E), R8.1
unnamed: R1.2, R6.1, U1.4 (-)
unnamed: R2.2, R3.2, U1.3 (+)
unnamed: R5.2, U1.1, U1.16
unnamed: R6.2, R10.2, R11.1, U1.8
unnamed: R11.2, R13.2, U1.14 (+)
unnamed: R12.2, R16.1, U1.13 (-)
unnamed: CUTCV1.2, R14.2
unnamed: CUTOFF1.2, R15.2
unnamed: CUTOFF1.3, R18.2
unnamed: R21.1, Res1.1

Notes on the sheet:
normalized to GND
"MS20" style Sallen key filter

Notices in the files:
README.md:
CC BY-SA 4.0
